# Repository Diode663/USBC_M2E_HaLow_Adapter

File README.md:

# USB-C to M.2 Key-E HaLow adapter

USB 2.0 over a USB-C receptacle to an M.2 2230 Key-E socket, for the Gateworks
GW16170 (Morse Micro MM8108-M20) Wi-Fi HaLow card. 56.5 x 40.5 mm, 2-layer
(JLCPCB JLC0216A), single-sided assembly.

> **Status: Rev A is built and works as designed** (boards assembled by JLCPCB, confirmed by the
> author on 2026-09-29). The project is closed; no Rev B is planned.
> Test procedure: [`docs/Test_Procedure.md`](docs/Test_Procedure.md). Pre-fabrication review:
> [`docs/Design_Review_2026-09-20.md`](docs/Design_Review_2026-09-20.md).

| Block | Parts |
|---|---|
| USB-C input | J1 HRO TYPE-C-31-M-12, R1/R2 5.1k CC pull-downs, U1 USBLC6-2SC6, D1 SMF5.0A |
| 3.3 V / 3 A buck | U2 TPS563201, L1 2.2 uH, C1/C2 in, C4/C5 out, R3/R4 33.2k/10k = 3.32 V |
| M.2 socket | J2 MLD-NGFF-E-4.2H, C6 100 uF, C7 10 uF, C8/C9 100 nF |
| Mechanical | H1-H4 M3, H5 SMTSOM225BTR M2 x 2.5 mm SMT nut for the card |

Only USB D+/D- (M.2 pins 3 and 5), 3.3 V and ground go to the card. W_DISABLE1# (the card's
reset) and W_DISABLE2# (wake) are left open on purpose: the card has its own pull-ups, and its
reset pin uses a power-on RC that an external pull-up would defeat.

## Bill of materials

Full BOM with notes and the parts you supply yourself: **[`BOM.md`](BOM.md)**.
The CSV that went to JLCPCB: [`fab/USBC_M2E_HaLow_Adapter_bom.csv`](fab/USBC_M2E_HaLow_Adapter_bom.csv).

| Ref | Qty | Value | Part number | LCSC |
|---|---|---|---|---|
| U2 | 1 | 3 A buck regulator | TPS563201DDCR | C116592 |
| U1 | 1 | USB ESD array | USBLC6-2SC6 | C7519 |
| D1 | 1 | 5 V TVS | SMF5.0A | C19077497 |
| L1 | 1 | 2.2 µH | CYA0630-2.2UH | C5189746 |
| J1 | 1 | USB-C receptacle | TYPE-C-31-M-12 | C165948 |
| J2 | 1 | M.2 Key-E socket, 4.2 mm | MLD-NGFF-E-4.2H | C52766479 |
| H5 | 1 | M2 x 2.5 mm SMT nut | SMTSOM225BTR | C5301773 |
| C1 | 1 | 10 µF 25 V, 1210 | GRM32DR71E106KA12L | C77100 |
| C6 | 1 | 100 µF 6.3 V, 1206 | CL31A107MQHNNNE | C15008 |
| C4, C5 | 2 | 22 µF 25 V, 0805 | CL21A226MAQNNNE | C45783 |
| C7 | 1 | 10 µF 10 V, 0603 | CL10A106KP8NNNC | C19702 |
| C2, C3, C8, C9 | 4 | 100 nF 16 V, 0402 | CL05B104KO5NNNC | C1525 |
| R1, R2 | 2 | 5.1 kΩ 1 %, 0402 | 0402WGF5101TCE | C25905 |
| R3 | 1 | 33.2 kΩ 1 %, 0402 | FRC0402F3322TS | C2930001 |
| R4 | 1 | 10 kΩ 1 %, 0402 | 0402WGF1002TCE | C25744 |

You also need the GW16170 card, an M2 x 3–4 mm screw, an MMCX antenna or pigtail, and a short
3 A USB-C cable on a port that can supply about 0.9 A.

## How it was made

Everything is generated from Python. Edit the scripts, not the KiCad files. Run with KiCad's Python:

    "C:\Program Files\KiCad\10.0\bin\python.exe" generate_schematic.py --force
    "C:\Program Files\KiCad\10.0\bin\python.exe" autoplace.py . --floorplan
    "C:\Program Files\KiCad\10.0\bin\python.exe" autoplace.py . --place --force
    "C:\Program Files\KiCad\10.0\bin\python.exe" setup_fab.py
    "C:\Program Files\KiCad\10.0\bin\python.exe" route_board.py
    "C:\Program Files\KiCad\10.0\bin\python.exe" drc_report.py
    "C:\Program Files\KiCad\10.0\bin\python.exe" check_m2_clearance.py
    "C:\Program Files\KiCad\10.0\bin\python.exe" build_package.py

`--place` resets every unlocked footprint. Designators moved by hand in KiCad are detected and
kept (`.pcbgen-refs.json`). `route_board.py` redraws every track, via and pour each time it runs.
`build_package.py` writes `fab/` and refuses to run unless DRC is clean.

Mechanical facts, from the MLD-NGFF-E-4.2H drawing:
- the card extends from the even-pin / locating-peg side of the socket;
- the card stop is 1.75 mm behind the pegs, so the 2230 notch is 29.75 mm from the socket centre;
- the card's underside is 2.52 mm above the board; parts under it must be 0.90 mm or lower.

JLCPCB: `setup_fab.py` writes their 2-layer rules into the project and into
`USBC_M2E_HaLow_Adapter.kicad_dru`, with the source pages and date in its docstring. The USB pair
is 0.3345 / 0.1524 mm with ground pour 0.2032 mm either side, from JLCPCB's own calculator for
stackup JLC0216A. JLCPCB does not test impedance on 2-layer boards. `jlc_rotations.json` holds
the placement-file corrections with the evidence for each.

## Repository contents
- `USBC_M2E_HaLow_Adapter.kicad_*`: the KiCad 10 project, schematic, routed board and custom design rules.
- `fab/`: the package sent to JLCPCB for Rev A (gerbers zip, BOM, placement file, order notes).
- `docs/`: schematic PDF, renders, copper images, the pre-fabrication design review and the board test procedure.
- `library/`: project symbols, footprints and 3D models.
- `*.py`: the generators. `schlib.py`, `subcircuits.py`, `pcblib.py`, `autoplace.py`, `recipes.py` and `jlc_cpl.py` are copies of the libraries the project was generated with.
- Vendor datasheets are not included.

## Licence

Copyright Diode663 2026.

**Hardware** (the KiCad project, schematic, board, the project's own symbols and footprints,
fabrication outputs and documentation): this source describes Open Hardware and is licensed under
the CERN-OHL-P v2. You may redistribute and modify this source and make products using it under
the terms of the CERN-OHL-P v2 (<https://ohwr.org/cern_ohl_p_v2.txt>), a copy of which is in
[`LICENSE`](LICENSE). This source is distributed WITHOUT ANY EXPRESS OR IMPLIED WARRANTY,
INCLUDING OF MERCHANTABILITY, SATISFACTORY QUALITY AND FITNESS FOR A PARTICULAR PURPOSE. Please
see the CERN-OHL-P v2 for applicable conditions.
Source location: <https://github.com/Diode663/USBC_M2E_HaLow_Adapter>

**Software** (every `*.py` file): MIT, see [`LICENSE-MIT`](LICENSE-MIT).

**Not covered by either licence** — third-party material, included for convenience and owned by
its respective rights holders:
- footprints and 3D models obtained from LCSC / EasyEDA with `easyeda2kicad`:
  `library/HaLowAdapter.pretty/CONN-SMD_MLD-NGFF-E-4.2H.kicad_mod`, `IND-SMD_L7.2-W6.6_GPSR07X0.kicad_mod`,
  `SMTSO_M2_H2.5_SMTSOM225BTR.kicad_mod`, and in `library/HaLowAdapter.3dshapes/` the
  `USB-C_SMD-TYPE-C-31-M-12_1`, `IND-SMD_L7.2-W6.6-H3.0_GPSR07X0` and `SMD_BD5.6-D3.6` models;
- `USB_C_Receptacle_HRO_TYPE-C-31-M-12.kicad_mod` and the M.2 socket symbol, which are modified
  copies from the KiCad libraries (CC-BY-SA 4.0 with the KiCad library exception).

Gateworks, Morse Micro, JLCPCB and the part manufacturers are not affiliated with this project.

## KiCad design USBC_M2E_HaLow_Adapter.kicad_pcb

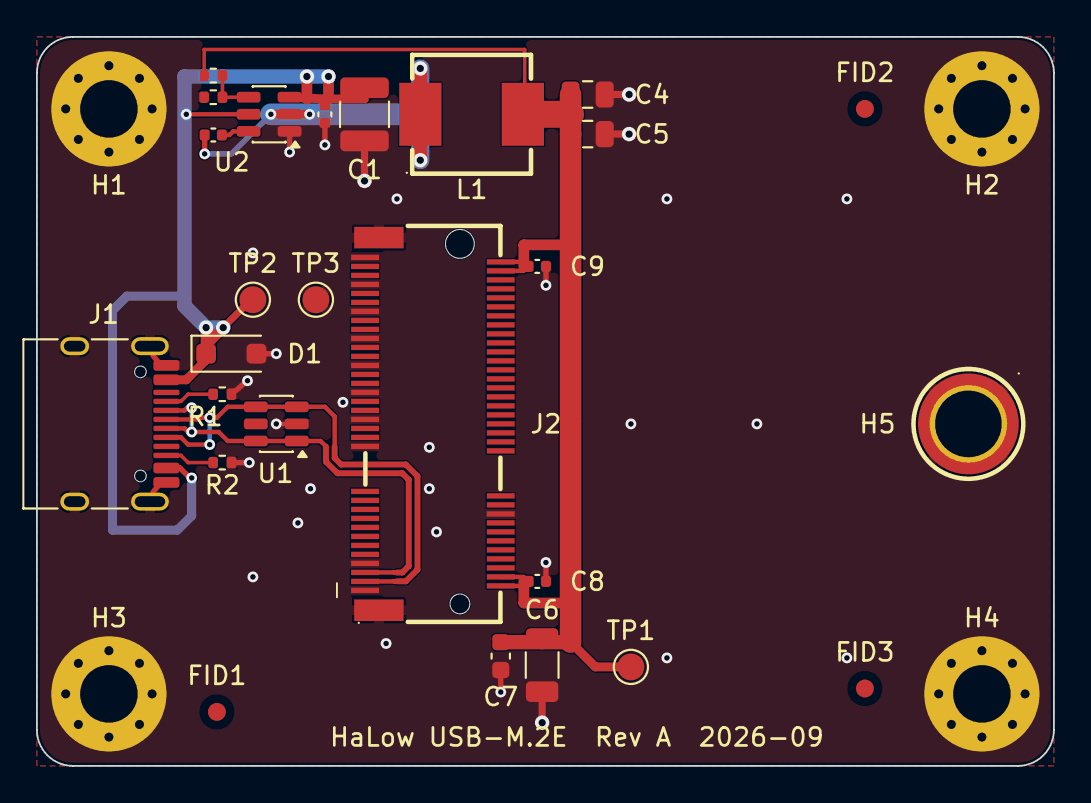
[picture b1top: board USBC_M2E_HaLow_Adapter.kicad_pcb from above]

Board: 2 copper layers, 56.5 x 40.5 mm, 30 parts (0 on the bottom side), 10 nets.

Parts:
C1: 10uF/25V; C_1210_3225Metric
C2, C3, C8, C9: 100nF; C_0402_1005Metric
C4, C5: 22uF; C_0805_2012Metric
C6: 100uF; C_1206_3216Metric
C7: 10uF; C_0603_1608Metric
D1: SMF5.0A; D_SOD-123F
FID1, FID2, FID3: Fiducial; Fiducial_1mm_Mask2mm
H1, H2, H3, H4: M3; MountingHole_3.2mm_M3_Pad_Via
H5: M2 standoff H2.5; SMTSO_M2_H2.5_SMTSOM225BTR
J1: USB-C; USB_C_Receptacle_HRO_TYPE-C-31-M-12
J2: M.2 Key-E (GW16170); CONN-SMD_MLD-NGFF-E-4.2H
L1: 2.2uH; IND-SMD_L7.2-W6.6_GPSR07X0
R1, R2: 5.1k; R_0402_1005Metric
R3: 33.2k; R_0402_1005Metric
R4: 10k; R_0402_1005Metric
TP1: +3V3; TestPoint_Pad_D1.5mm
TP2: VBUS; TestPoint_Pad_D1.5mm
TP3: GND; TestPoint_Pad_D1.5mm
U1: USBLC6-2SC6; SOT-23-6
U2: TPS563201DDCR; SOT-23-6

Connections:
+3V3: C4.1, C5.1, C6.1, C7.1, C8.1, C9.1, J2.2, J2.4, J2.72, J2.74, L1.2, R3.1, TP1.1
/CC1: J1.A5, R1.1
/CC2: J1.B5, R2.1
/FB: R3.2, R4.1, U2.4
/SW: C3.1, L1.1, U2.2
/USB_D_N: J1.A7, J1.B7, J2.5, U1.1, U1.6
/USB_D_P: J1.A6, J1.B6, J2.3, U1.3, U1.4
/VBST: C3.2, U2.6
GND: C1.2, C2.2, C4.2, C5.2, C6.2, C7.2, C8.2, C9.2, D1.2, H1.1, H2.1, H3.1, H4.1, H5.1, J1.A1, J1.A12, J1.B1, J1.B12, J1.SH, J2.1, J2.7, J2.18, J2.33, J2.39, J2.45, J2.51, J2.57, J2.63, J2.69, J2.75, J2.76, J2.77, R1.2, R2.2, R4.2, TP3.1, U1.2, U2.1
VBUS: C1.1, C2.1, D1.1, J1.A4, J1.A9, J1.B4, J1.B9, TP2.1, U2.3, U2.5

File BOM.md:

# Bill of materials — Rev A

Machine-readable copy, exactly as uploaded to JLCPCB: [`fab/USBC_M2E_HaLow_Adapter_bom.csv`](fab/USBC_M2E_HaLow_Adapter_bom.csv).
Placement file: [`fab/USBC_M2E_HaLow_Adapter_cpl.csv`](fab/USBC_M2E_HaLow_Adapter_cpl.csv).

## Assembled by JLCPCB (15 lines, 20 parts, all top side)

| Ref | Qty | Value | Part number | Manufacturer | Package | LCSC |
|---|---|---|---|---|---|---|
| U2 | 1 | 3 A synchronous buck, 3.3 V rail | TPS563201DDCR | Texas Instruments | SOT-23-6 | C116592 |
| U1 | 1 | USB 2.0 ESD array | USBLC6-2SC6 | STMicroelectronics | SOT-23-6 | C7519 |
| D1 | 1 | 5 V TVS on VBUS | SMF5.0A | R+O | SOD-123FL | C19077497 |
| L1 | 1 | 2.2 µH, 7 A / 10 A sat, 15.5 mΩ | CYA0630-2.2UH | SHOU HAN | 7.2 x 6.6 x 3.0 mm | C5189746 |
| J1 | 1 | USB-C receptacle, USB 2.0, 16 pin | TYPE-C-31-M-12 | HRO (Korean Hroparts) | SMD, right angle | C165948 |
| J2 | 1 | M.2 Key-E socket, 4.2 mm high | MLD-NGFF-E-4.2H | MLD (Minlenda) | SMD, 67 pin | C52766479 |
| H5 | 1 | M2 x 2.5 mm SMT nut, card standoff | SMTSOM225BTR | YIYUAN | 5.6 mm body, 3.7 mm hole | C5301773 |
| C1 | 1 | 10 µF 25 V X7R | GRM32DR71E106KA12L | Murata | 1210 | C77100 |
| C6 | 1 | 100 µF 6.3 V X5R | CL31A107MQHNNNE | Samsung Electro-Mechanics | 1206 | C15008 |
| C4, C5 | 2 | 22 µF 25 V X5R | CL21A226MAQNNNE | Samsung Electro-Mechanics | 0805 | C45783 |
| C7 | 1 | 10 µF 10 V X5R | CL10A106KP8NNNC | Samsung Electro-Mechanics | 0603 | C19702 |
| C2, C3, C8, C9 | 4 | 100 nF 16 V X7R | CL05B104KO5NNNC | Samsung Electro-Mechanics | 0402 | C1525 |
| R1, R2 | 2 | 5.1 kΩ 1 % | 0402WGF5101TCE | Uniroyal | 0402 | C25905 |
| R3 | 1 | 33.2 kΩ 1 % | FRC0402F3322TS | Uniroyal | 0402 | C2930001 |
| R4 | 1 | 10 kΩ 1 % | 0402WGF1002TCE | Uniroyal | 0402 | C25744 |

Notes
- J1, J2 and H5 are listed by JLCPCB as "SMT Assembly, PCBA Type: Economic and Standard" (checked 2026-09-20). All three, and most of the ICs, are Extended-library parts.
- The CSV sent to JLCPCB names the Samsung capacitors' manufacturer as "CCTC". JLCPCB matches on the LCSC number, so the order is unaffected; the table above has the correct maker.
- L1 is 2.2 µH on purpose: TI's table for the TPS563201 gives 2.2 µH typical at 3.3 V, and with the socket's bulk capacitor on the same rail it keeps the output filter inside TI's range. See `docs/Design_Review_2026-09-20.md`.

## On the board but not populated

| Ref | What | Footprint |
|---|---|---|
| H1–H4 | M3 mounting holes, plated and grounded | 3.2 mm hole, 6.4 mm pad |
| FID1–FID3 | 1 mm fiducials | — |
| TP1, TP2, TP3 | 1.5 mm test pads: +3V3, VBUS, GND | — |

## You supply

| Qty | Item | Notes |
|---|---|---|
| 1 | Gateworks GW16170 Wi-Fi HaLow card | M.2 2230 Key-E, USB 2.0 on pins 3/5, 3.3 V only. The GW16167 has the same pinout. The GW16159 is SDIO-only and will not work. |
| 1 | M2 x 3 mm or 4 mm pan-head screw | Holds the card to H5. |
| 1 | MMCX antenna or MMCX pigtail | The antenna connector is on the card, not on this board. 902–928 MHz. |
| 1 | USB-C cable rated 3 A, short | The card can pull about 0.9 A from VBUS in transmit bursts (estimate). Use a USB 3 / USB-C host port or a powered hub, not a 500 mA USB 2.0 port. |
| 4 | M3 screws and standoffs | Optional, for mounting. |

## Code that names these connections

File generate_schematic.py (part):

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        x, y = 215.9, 101.6
        put(U2, x, y)
        vin, en = s.pin(U2, "VIN"), s.pin(U2, "EN")
        sw, bst, fb = s.pin(U2, "SW"), s.pin(U2, "VBST"), s.pin(U2, "VFB")
        # input rail: VBUS port, bulk, HF cap, EN tied to VIN
        x_en, x_c2, x_c1, x_in = vin[0] - 5.08, vin[0] - 15.24, vin[0] - 30.48, vin[0] - 40.64
        s.wire(vin, (x_in, vin[1]))
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        s.wire(c3t, (x_bst, top))
        s.wire(bst, (x_bst, bst[1]), c3b)
        s.label("SW", l1[0] - 5.08, top)
        s.label("VBST", bst[0] + 6.35, bst[1])
        # output node: rail port, divider, output caps, ERC flag
        xo = l2[0] + 7.62
        s.wire(l2, (xo, top))
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    with s.block("M.2 KEY-E SOCKET (J2) - GATEWORKS GW16170, USB 2.0 ONLY"):
        x, y = 388.62, 127.0
        put(J2, x, y)
        s.stub(J2, "3", 7.62, label="USB_D_P")
        s.stub(J2, "5", 7.62, label="USB_D_N")
        s.stub(J2, "2", 2.54, power="+3V3")
        g = s.stub(J2, "1", 5.08, power="GND")
        sh = s.pin(J2, "76")
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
